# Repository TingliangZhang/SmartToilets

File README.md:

# SmartToilets
智能粪坑

## STM32

STM32选型：STM32G031K8T6 STM32G031J6M6

[STM32G031J6 ](https://www.st.com/en/microcontrollers-microprocessors/stm32g031j6.html)

Internal 16 MHz RC with PLL option 这玩意内部时钟16M感觉不用加外部时钟了，除非用得到48MHz

BOOT0用10k电阻拉低接地，boot from User Flash memory

加一个RST按钮，按下拉低RST

加入一个电源指示LED，以及一个接到PB9的LED

烧写用4pin杜邦线母头，接0/3.3V/TX/RX，使用ST-Link烧写程序

## 手势传感器

[APDS-9960](https://www.broadcom.com/products/optical-sensors/integrated-ambient-light-and-proximity-sensors/apds-9960)

淘宝卖5.2一个

## 电路

## 成本估计

| 品名                | 目前购买价（RMB） | 量产价 |
| ------------------- | ----------------- | ------ |
| APDS-9960           | 5.2               |        |
| STM32G031K8T6       | 4.81              |        |
| DRV8837C            | 0.5561            |        |
| TLV62568DBV         | 1.0181            |        |
| N25电机和其他连接件 | 2                 |        |
| PCB                 | 1                 |        |

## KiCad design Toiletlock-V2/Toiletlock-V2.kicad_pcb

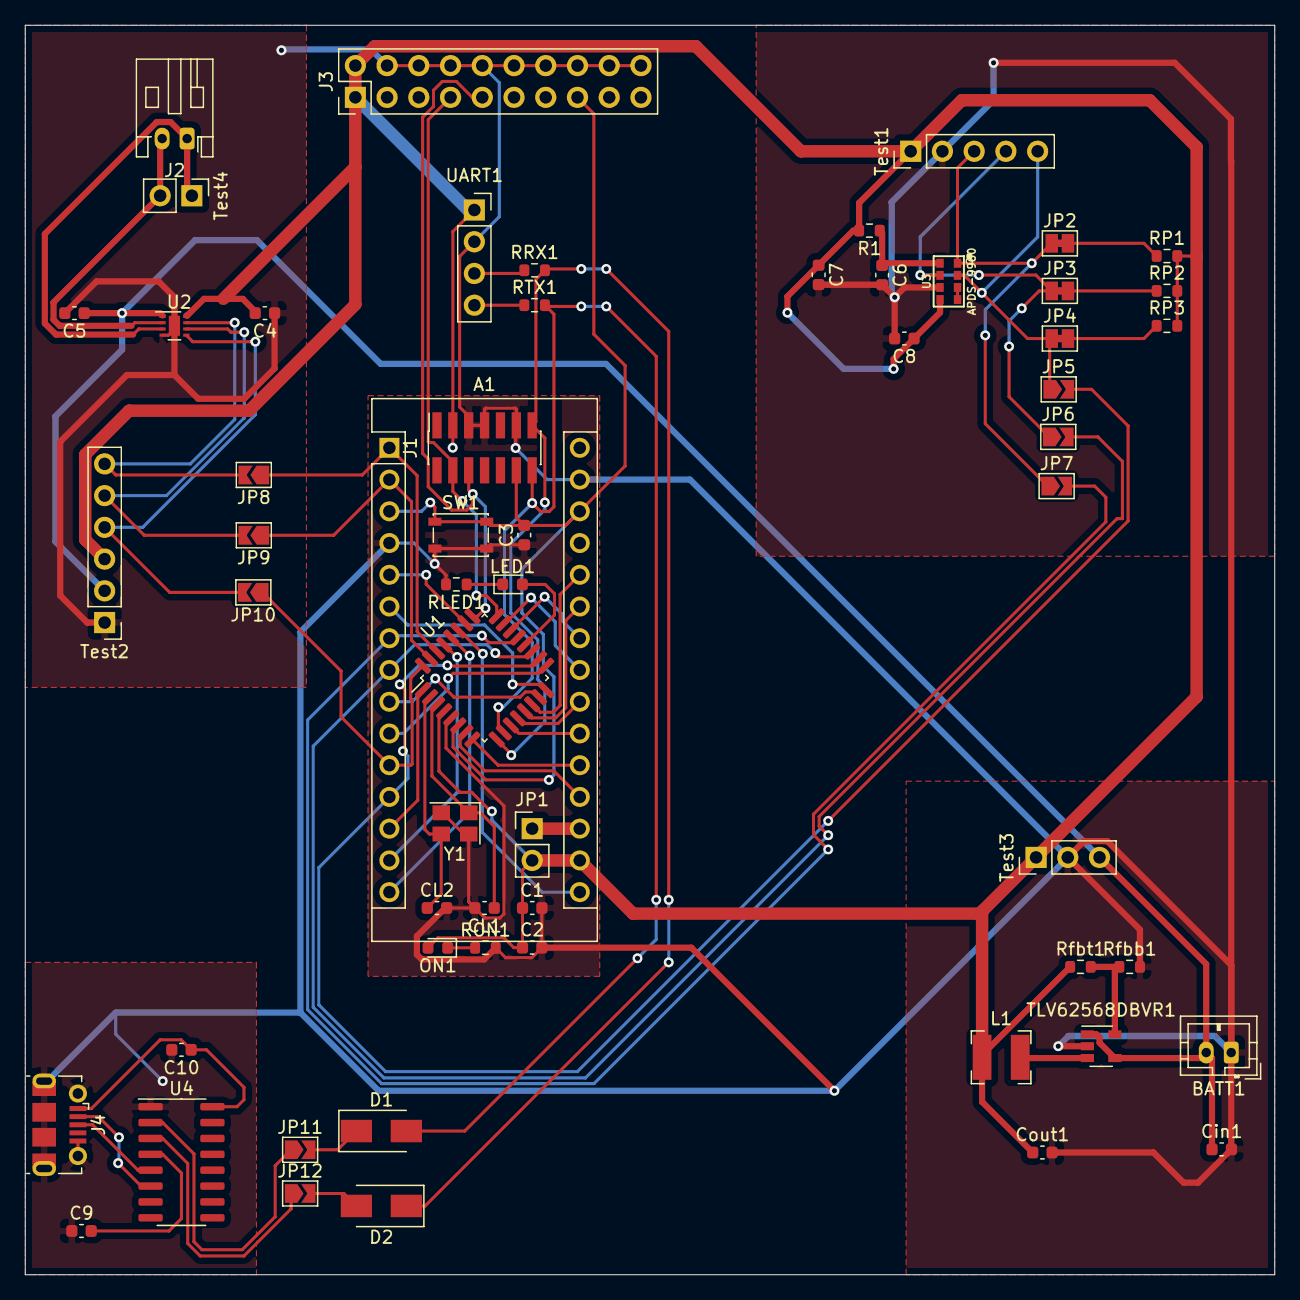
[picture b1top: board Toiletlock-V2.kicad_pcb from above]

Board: 2 copper layers, 100.0 x 100.0 mm, 59 parts (0 on the bottom side), 61 nets.

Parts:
A1: Arduino_Nano_v2.x; Arduino_Nano
BATT1: Conn_01x02_Male; JST_PH_B2B-PH-K_1x02_P2.00mm_Vertical
C1: 4.7uF; C_0603_1608Metric
C2, C3: 100nF; C_0603_1608Metric
C4, C5, C9, C10: 0.1uF; C_0603_1608Metric
C6, C8: 1uF; C_0603_1608Metric
C7: CP 10uF; C_0603_1608Metric
CL1, CL2: 20pF; C_0603_1608Metric
Cin1: 4.7uF; C_0603_1608Metric
Cout1: 10uF; C_0603_1608Metric
D1, D2: D_Schottky; D_SMA
J1: Conn_ST_STDC14; PinSocket_2x07_P1.27mm_Vertical_SMD
J2: Conn_01x02_Male; JST_PH_S2B-PH-K_1x02_P2.00mm_Horizontal
J3: Conn_ARM_JTAG_SWD_20; PinHeader_2x10_P2.54mm_Vertical
J4: USB_B_Micro; USB_Micro-B_Molex-105017-0001
JP1: Jumper; PinHeader_1x02_P2.54mm_Vertical
JP2, JP3, JP4: SolderJumper_2_Bridged; SolderJumper-2_P1.3mm_Bridged_Pad1.0x1.5mm
JP5, JP6, JP7, JP8, JP9, JP10, JP11, JP12: SolderJumper_2_Open; SolderJumper-2_P1.3mm_Open_TrianglePad1.0x1.5mm
L1: 2.2uH 2.6A; L_Bourns-SRN4018
LED1: LED; LED_0603_1608Metric
ON1: LED; LED_0603_1608Metric
R1: 22R; R_0603_1608Metric
RLED1: 1k; R_0603_1608Metric
RON1: 1k; R_0603_1608Metric
RP1, RP2: 4.7k; R_0603_1608Metric
RP3: 10k; R_0603_1608Metric
RRX1: 22R; R_0603_1608Metric
RTX1: 22R; R_0603_1608Metric
Rfbb1: 100k; R_0603_1608Metric
Rfbt1: 453k; R_0603_1608Metric
SW1: SW_Push; SW_SPST_PTS810
TLV62568DBVR1: TLV62568DBV; SOT-23-5
Test1: Conn_01x05; PinHeader_1x05_P2.54mm_Vertical
Test2: Conn_01x06; PinHeader_1x06_P2.54mm_Vertical
Test3: Conn_01x03; PinHeader_1x03_P2.54mm_Vertical
Test4: Conn_01x02; PinHeader_1x02_P2.54mm_Vertical
U1: STM32G031K8T3; LQFP-32_7x7mm_P0.8mm
U2: DRV8837C; WSON-8-1EP_2x2mm_P0.5mm_EP0.9x1.6mm
U3: APDS-9960
U4: CH340C; SOIC-16_3.9x9.9mm_P1.27mm
UART1: Conn_01x04_Female; PinSocket_1x04_P2.54mm_Vertical
Y1: Crystal_GND24; Crystal_SMD_3225-4Pin_3.2x2.5mm

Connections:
+3V3: A1.17, C1.1, C2.1, C4.2, C7.1, C8.1, Cout1.1, J1.3, J3.1, J3.2, JP1.2, L1.2, ON1.2, R1.2, RP1.2, RP2.2, RP3.2, Rfbt1.1, Test1.1, Test2.3, Test3.1, U1.4, U2.8, U3.5, UART1.1
+3V8: BATT1.2, C5.1, Cin1.1, TLV62568DBVR1.1, TLV62568DBVR1.4, Test2.2, Test3.3, U2.1
/NRST: A1.3, A1.28, C3.2, J1.12, J3.15, SW1.1, U1.6
/PA0: A1.19, U1.7
/PA1: A1.20, U1.8
/PA4: A1.21, U1.11
/PA5: A1.22, U1.12
/PA6: A1.25, U1.13
/PA7: A1.26, U1.14
/PA8: A1.12, JP5.2, U1.18
/PA9: A1.8, JP6.2, U1.19
/PA10: A1.7, JP7.2, U1.21
/PA11: A1.24, U1.22
/PA12: A1.23, U1.23
/PA15: A1.5, U1.26
/PB0: A1.9, U1.15
/PB1: A1.6, U1.16
/PB2: A1.10, U1.17
/PB3: A1.16, U1.27
/PB4: A1.15, U1.28
/PB5: A1.14, U1.29
/PB6: A1.1, JP8.1, U1.30
/PB7: A1.2, JP9.1, U1.31
/PB8: A1.11, JP10.1, U1.32
/PB9: A1.13, U1.1
/PC6: LED1.2, U1.20
/SWCLK: J1.6, J3.9, U1.25
/SWDIO: J1.4, J3.7, U1.24
GND: A1.4, A1.29, BATT1.1, C1.2, C2.2, C3.1, C4.1, C5.2, C6.2, C7.2, C8.2, C9.1, C10.2, CL1.2, CL2.2, Cin1.2, Cout1.2, J1.5, J1.7, J1.11, J3.4, J3.6, J3.8, J3.10, J3.12, J3.14, J3.16, J3.18, J3.20, J4.5, J4.6, RLED1.2, RON1.2, Rfbb1.2, SW1.2, TLV62568DBVR1.2, Test1.2, Test2.1, Test3.2, U1.5, U2.4, U2.9, U3.6, U4.1, UART1.2, Y1.2, Y1.4
unnamed: A1.18, JP1.1
unnamed: C6.1, R1.1, U3.8
unnamed: C9.2, U4.4
unnamed: CL1.1, U1.3, Y1.1
unnamed: CL2.1, U1.2, Y1.3
unnamed: D1.1, JP11.2
unnamed: D2.2, JP12.2
unnamed: J2.1, Test4.1, U2.3
unnamed: J2.2, Test4.2, U2.2
unnamed: J4.2, U4.6
unnamed: J4.3, U4.5
unnamed: JP2.1, JP7.1, Test1.3, U3.1
unnamed: JP2.2, RP1.1
unnamed: JP3.1, JP6.1, Test1.4, U3.7
unnamed: JP3.2, RP2.1
unnamed: JP4.1, JP5.1, Test1.5, U3.2
unnamed: JP4.2, RP3.1
unnamed: JP8.2, Test2.6, U2.7
unnamed: JP9.2, Test2.5, U2.6
unnamed: JP10.2, Test2.4, U2.5
unnamed: JP11.1, U4.2
unnamed: JP12.1, U4.3
unnamed: L1.1, TLV62568DBVR1.3
unnamed: LED1.1, RLED1.1
unnamed: ON1.1, RON1.1
unnamed: RRX1.1, UART1.3
unnamed: RTX1.1, UART1.4
unnamed: Rfbb1.1, Rfbt1.2, TLV62568DBVR1.5
unnamed: U3.3, U3.4
T_VCP_RX: D1.2, J1.14, RTX1.2, U1.10
T_VCP_TX: D2.1, J1.13, RRX1.2, U1.9
VBUS: C10.1, J4.1, U4.16

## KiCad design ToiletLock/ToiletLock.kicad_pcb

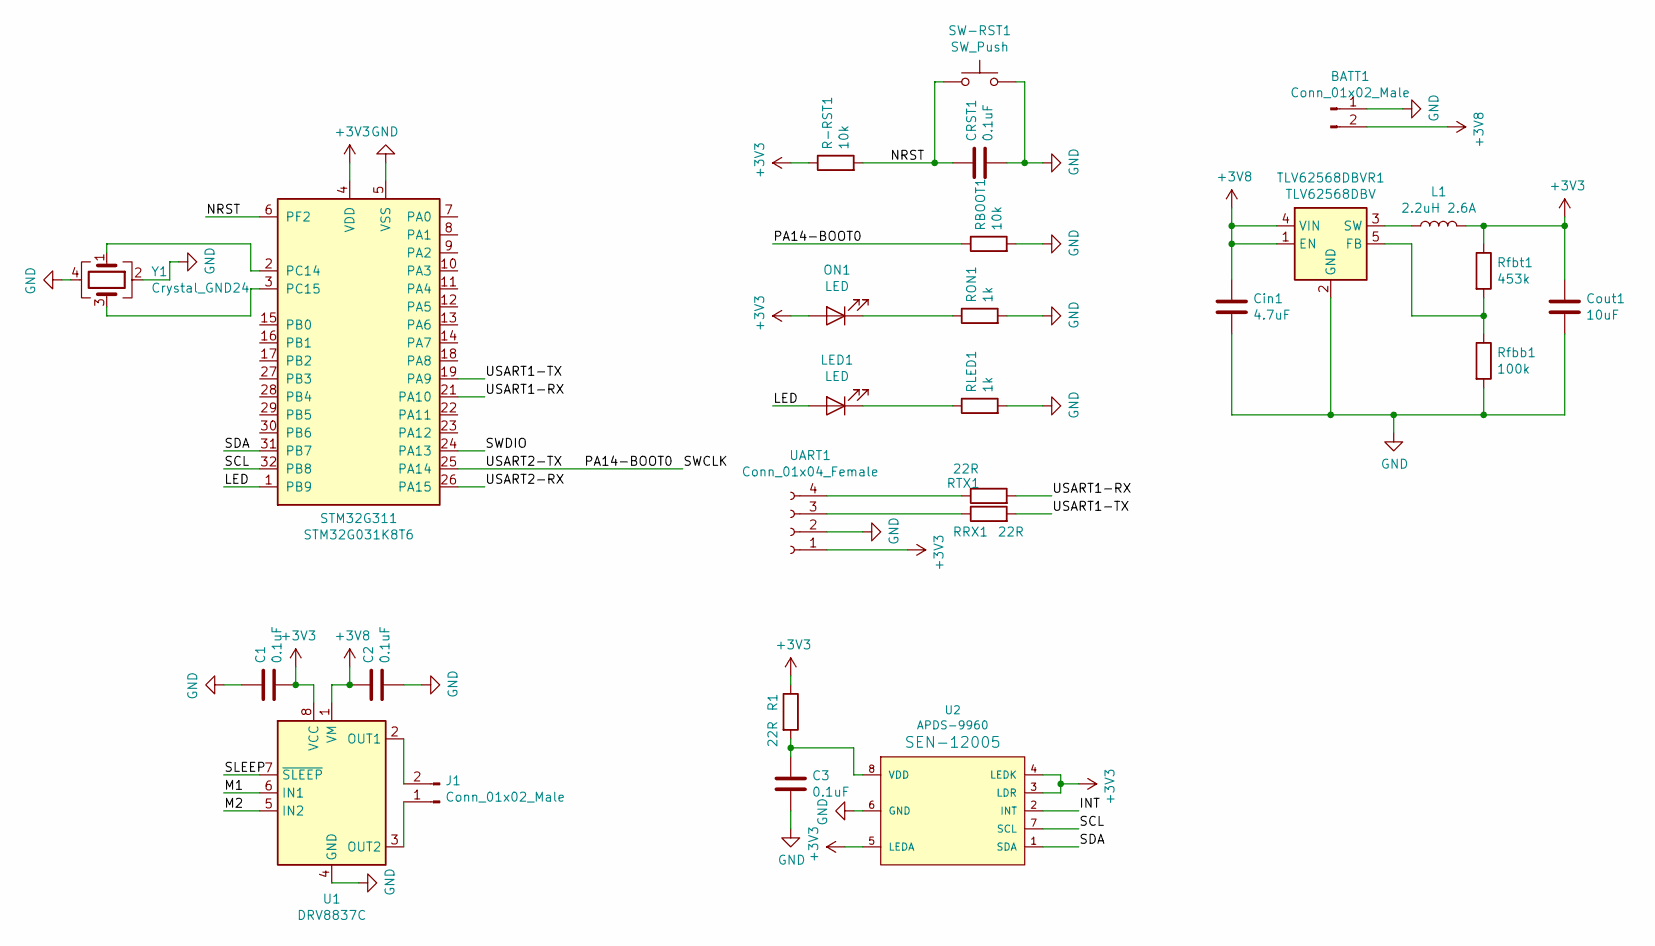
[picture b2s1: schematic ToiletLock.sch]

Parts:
BATT1: Conn_01x02_Male; JST_PH_B2B-PH-K_1x02_P2.00mm_Vertical
C1, C2, C3: 0.1uF; C_0603_1608Metric
CRST1: 0.1uF; C_0603_1608Metric
Cin1: 4.7uF; C_0603_1608Metric
Cout1: 10uF; C_0603_1608Metric
J1: Conn_01x02_Male; JST_PH_S2B-PH-K_1x02_P2.00mm_Horizontal
L1: 2.2uH 2.6A; L_Bourns-SRN4018
LED1: LED; LED_0603_1608Metric
ON1: LED; LED_0603_1608Metric
R1: 22R; R_0603_1608Metric
R-RST1: 10k; R_0603_1608Metric
RBOOT1: 10k; R_0603_1608Metric
RLED1: 1k; R_0603_1608Metric
RON1: 1k; R_0603_1608Metric
RRX1: 22R; R_0603_1608Metric
RTX1: 22R; R_0603_1608Metric
Rfbb1: 100k; R_0603_1608Metric
Rfbt1: 453k; R_0603_1608Metric
STM32G311: STM32G031K8T6; LQFP-32_7x7mm_P0.8mm
SW-RST1: SW_Push; TACTILE_SWITCH_SMD_6.0X3.5MM
TLV62568DBVR1: TLV62568DBV; SOT-23-5
U1: DRV8837C; WSON-8-1EP_2x2mm_P0.5mm_EP0.9x1.6mm
U2: APDS-9960
UART1: Conn_01x04_Female; PinSocket_1x04_P2.54mm_Vertical
Y1: Crystal_GND24; Crystal_SMD_3225-4Pin_3.2x2.5mm

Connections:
+3V3: C1.2, Cout1.1, L1.2, ON1.2 (A), R1.1, R-RST1.1, Rfbt1.1, STM32G311.4 (VDD), U1.8 (VCC), U2.3 (LDR), U2.4 (LEDK), U2.5 (LEDA), UART1.1
+3V8: BATT1.2, C2.1, Cin1.1, TLV62568DBVR1.1 (EN), TLV62568DBVR1.4 (VIN), U1.1 (VM)
/INT: U2.2 (INT)
/LED: LED1.2 (A), STM32G311.1 (PB9)
/M1: U1.6 (IN1)
/M2: U1.5 (IN2)
/NRST: CRST1.1, R-RST1.2, STM32G311.6 (PF2), SW-RST1.1
/PA14-BOOT0: RBOOT1.1, STM32G311.25 (PA14)
/SCL: STM32G311.32 (PB8), U2.7 (SCL)
/SDA: STM32G311.31 (PB7), U2.1 (SDA)
/SLEEP: U1.7 (~SLEEP)
/SWDIO: STM32G311.24 (PA13)
/USART1-RX: RTX1.2, STM32G311.21 (PA10)
/USART1-TX: RRX1.2, STM32G311.19 (PA9)
/USART2-RX: STM32G311.26 (PA15)
GND: BATT1.1, C1.1, C2.2, C3.2, CRST1.2, Cin1.2, Cout1.2, RBOOT1.2, RLED1.2, RON1.2, Rfbb1.2, STM32G311.5 (VSS), SW-RST1.2, TLV62568DBVR1.2 (GND), U1.4 (GND), U1.9 (GND), U2.6 (GND), UART1.2, Y1.2, Y1.4
unnamed: C3.1, R1.2, U2.8 (VDD)
unnamed: J1.1, U1.3 (OUT2)
unnamed: J1.2, U1.2 (OUT1)
unnamed: L1.1, TLV62568DBVR1.3 (SW)
unnamed: LED1.1 (K), RLED1.1
unnamed: ON1.1 (K), RON1.1
unnamed: RRX1.1, UART1.3
unnamed: RTX1.1, UART1.4
unnamed: Rfbb1.1, Rfbt1.2, TLV62568DBVR1.5 (FB)
unnamed: STM32G311.2 (PC14), Y1.1
unnamed: STM32G311.3 (PC15), Y1.3

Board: 2 copper layers, 27 parts (0 on the bottom side), 21 nets, no tracks yet.

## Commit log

2020-11-04 iniPCB
2020-11-04 Finish PCB
2021-01-29 del useless file
2021-01-29 sym_lib_table
2021-01-29 ToiletLock V2
2021-01-29 V2Sch
2021-01-29 module
2021-01-29 Dev board finish
2021-01-29 arrange peripheral
2021-01-29 tomorrow continue
2021-01-30 finish!
